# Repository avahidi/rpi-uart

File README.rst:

rpi-uart
========

This UART board for the Raspberry Pi, is one of those Sunday morning projects that turned out to be quite useful.
It lets you to power and talk to the board using only a micro-USB cable. Hence you can go from this mess

.. image:: doc/before.jpg
    :alt: connecting to the rpi using a serial to USB cable

. . . to this:

.. image:: doc/after.jpg
    :alt: connecting to the rpi using this board

To me the main advantage of this is that I can quickly move it between different boards.

Open hardware
-------------

The PCB was developed using KiCad and is published under the CERN Open Hardware License v1.2.

.. image:: doc/pcb.jpg

Some footprints have been modified to eliminate oval plated holes which may be expensive to manufacture.
I have also tried to make the design easy to solder, although you may still find the fine-pitch USB connector a bit challenging.
The CH340g IC was chosen to avoid depending on FTDI or counterfeit FTDI chips.

Operations modes
----------------

The board can be populated in a couple of ways to allow different powering modes.
Only one of which will not fry your Raspberry Pi so pay attention to this!

.. image:: doc/schematics.png

RPi mode
~~~~~~~~

To connect directly to a Raspberry Pi you should populate the following components::

     component |          type          | notes
    ========================================================
     J2        | micro USB connector    |
     U1        | CH340g                 |
     Y1        | 12MHz crystal          |
     C1,C2     | 22pF 0805 SMD caps     | probably optional
     R2        | 10K 0805 SMD resistor  | optional
     D1        | 0805 LED               | optional
     J5        | solder bridge          | bridge
     J4        | solder bridge          | MUST BE OPEN

If you want to power it from the same cable, you will also need these::

     component |          type          | notes
    ========================================================
     C4        | 22u SMD cap            |
     SW1       | Switch                 | or bridge 1-2 for permanent power

Full 5.0v mode
~~~~~~~~~~~~~~~

If you are using this as a stand-alone USB-to-serial converter and WITHOUT a raspberry pi
and want to have 5.0v transmit and receive signals you will need to bridge the 5.0 and 3.3 rails::

     component |          type          | notes
    ========================================================
     J5        | solder bridge          | MUST BE OPEN
     J4        | solder bridge          | bridge

Local 3.3v mode
~~~~~~~~~~~~~~~

If you instead want to use a locally generated 3.3v::

     component |          type          | notes
    ========================================================
     J5        | solder bridge          | MUST BE OPEN
     J4        | solder bridge          | MUST BE OPEN
     U2        | 3.3v SMD regulator     |
     C3, C5    | 100n 0805 SMD caps     |

Remaining components
~~~~~~~~~~~~~~~~~~~~

The following components are not needed and should not be populated::

     component |          type          | notes
    ========================================================
     D4        | protection SMD didoe   | protection for cheap regulators
     R3, R4    | 10K 0805 SMD resistors | for RX/TX LED
     D2, D3    | 0805 SMD LEDs          | RX/TX LED

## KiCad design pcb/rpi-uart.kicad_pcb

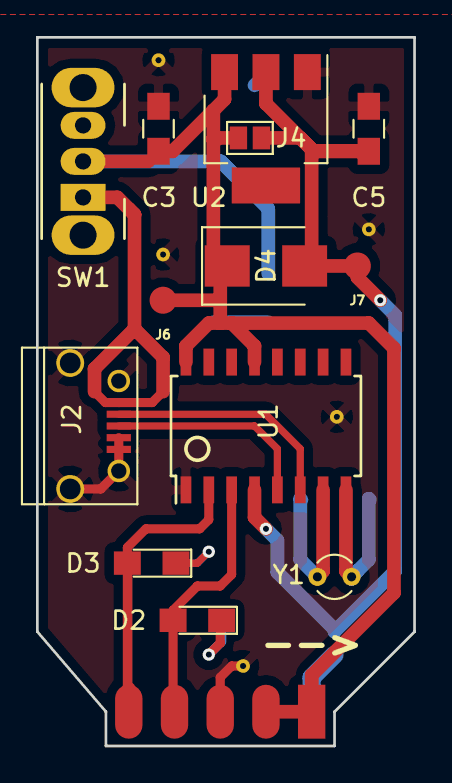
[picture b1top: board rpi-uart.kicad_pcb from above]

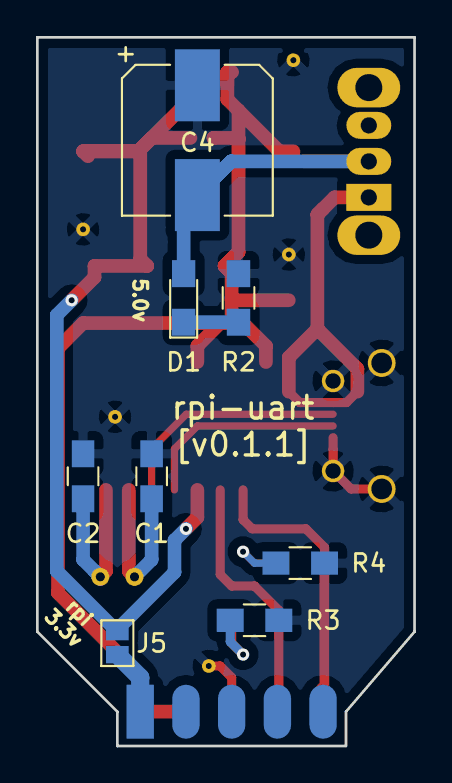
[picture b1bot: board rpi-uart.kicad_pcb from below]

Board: 2 copper layers, 21.0 x 39.4 mm, 28 parts (9 on the bottom side), 14 nets.

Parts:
C1, C2: 22p; C_0805_HandSoldering
C3, C5: 100n; C_0805_HandSoldering
C4: 22u; CP_Elec_8x10
D1, D2, D3: LED; LED_0805_HandSoldering
D4: D; D_SMB
J1, J3: Conn_01x05; pads_01x05
J2: USB_OTG; USB_Micro-B
J4, J5: GS2
J6: 5v; Measurement_Point_Round-SMD-Pad_Small
J7: 3.3v; Measurement_Point_Round-SMD-Pad_Small
R2, R3, R4: 10K; R_0805_HandSoldering
SW1: SW_Push_SPDT; SW_CuK_OS102011MA1QN1_SPDT_Angled
U1: CH340g; SOIC-16W_5.3x10.2mm_Pitch1.27mm
U2: TLV1117-33; SOT-223
U3, U4, U5, U6, U7: Via; via
Y1: 12MHz; Crystal_C26-LF_d2.1mm_l6.5mm_Vertical

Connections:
GND: C1.2, C2.2, C3.1, C4.1, C5.1, J1.3, J2.4, J2.5, J2.6, R3.2, R4.2, U1.1, U2.1, U3.1, U4.1, U5.1, U6.1, U7.1
unnamed: C1.1, U1.7, Y1.1
unnamed: C2.1, U1.8, Y1.2
unnamed: D1.1, R2.1
unnamed: D2.1, R3.1
unnamed: D3.1, R4.1
unnamed: J2.1, SW1.1
unnamed: J3.1, J5.1
RXD0: D3.2, J1.5, U1.2
TXD0: D2.2, J1.4, U1.3
USBD+: J2.3, U1.5
USBD-: J2.2, U1.6
VCC33: C5.2, D4.2, J4.1, J5.2, J7.1, U1.4, U2.2
VCC50: C3.2, C4.2, D1.2, D4.1, J1.1, J1.2, J4.2, J6.1, SW1.2, U1.13, U1.16, U2.3

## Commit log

2017-10-25 project created
2017-10-25 Added the PCB project
2017-10-25 added docs, corrected missing GND in schematics
2017-10-25 resized images manually
2017-10-29 v0.1.1: added missing silk, updated docs and images
2018-09-03 removed pcb link
